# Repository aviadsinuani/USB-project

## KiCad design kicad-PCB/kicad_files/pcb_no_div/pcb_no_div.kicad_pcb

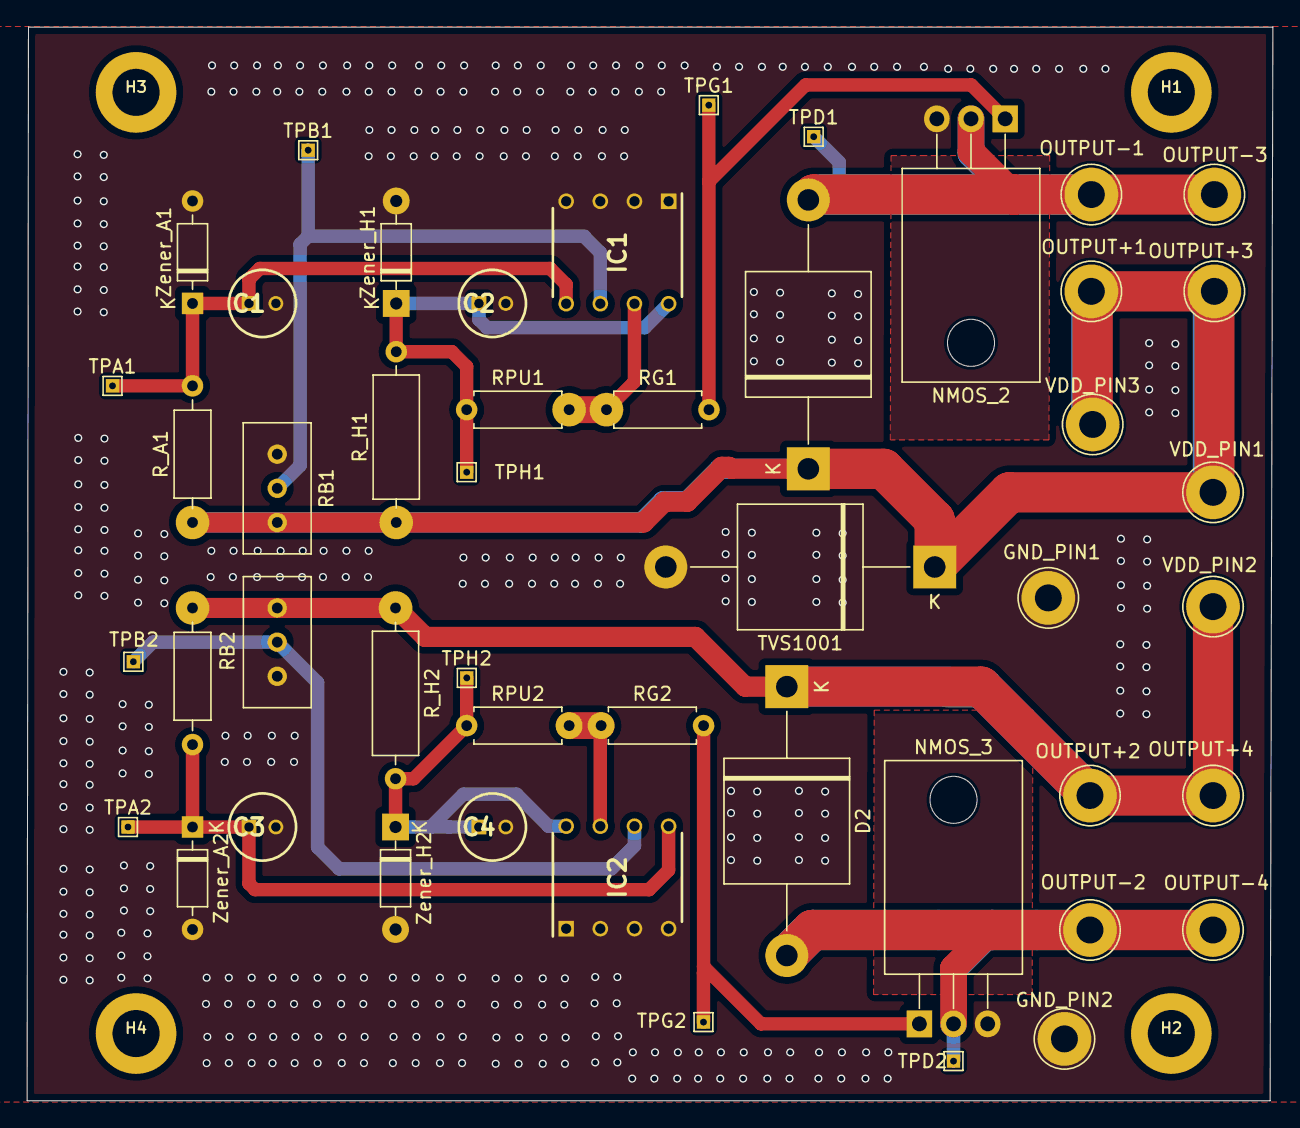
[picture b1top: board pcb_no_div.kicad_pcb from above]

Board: 2 copper layers, 92.7 x 79.9 mm, 52 parts (0 on the bottom side), 15 nets.

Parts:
C1, C2, C3, C4: C_Polarized; CAPPRD200W52D500H1250
D1, D2: 5KP28A; D_P600_R-6_P20.00mm_Horizontal
GND_PIN1, GND_PIN2: TestPoint_THTPad_D4.0mm_Drill2.0mm
H1, H2, H3, H4: MountingHole; screwHole
IC1, IC2: AS393P-E1; DIP762W56P254L930H431Q8N
NMOS_2, NMOS_3: NMOS; TO-220-3_Horizontal_TabDown
OUTPUT+1, OUTPUT+2, OUTPUT+3, OUTPUT+4: TestPoint_THTPad_D4.0mm_Drill2.0mm
OUTPUT-1, OUTPUT-2, OUTPUT-3, OUTPUT-4: TestPoint_THTPad_D4.0mm_Drill2.0mm
RB1, RB2: R_Potentiometer_Trim_US; Potentiometer_Bourns_3296W_Vertical
RG1, RG2: 2.5k; R_Axial_DIN0207_L6.3mm_D2.5mm_P7.62mm_Horizontal
RPU1, RPU2: 2.5k; R_Axial_DIN0207_L6.3mm_D2.5mm_P7.62mm_Horizontal
R_A1, R_A2: 2.5k; R_Axial_DIN0207_L6.3mm_D2.5mm_P10.16mm_Horizontal
R_H1, R_H2: 1K; R_Axial_DIN0309_L9.0mm_D3.2mm_P12.70mm_Horizontal
TPA1, TPA2: A_point; TestPoint_THTPad_1.0x1.0mm_Drill0.5mm
TPB1, TPB2: B_point; TestPoint_THTPad_1.0x1.0mm_Drill0.5mm
TPD1, TPD2: Output-; TestPoint_THTPad_1.0x1.0mm_Drill0.5mm
TPG1, TPG2: Gate; TestPoint_THTPad_1.0x1.0mm_Drill0.5mm
TPH1, TPH2: H_point; TestPoint_THTPad_1.0x1.0mm_Drill0.5mm
TVS1001: 100V; D_P600_R-6_P20.00mm_Horizontal
VDD_PIN1, VDD_PIN2, VDD_PIN3: TestPoint_THTPad_D4.0mm_Drill2.0mm
Zener_A1, Zener_A2: 11V; D_DO-35_SOD27_P7.62mm_Horizontal
Zener_H1, Zener_H2: 16V; D_DO-35_SOD27_P7.62mm_Horizontal

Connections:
GND: C1.2, C2.2, C3.2, C4.2, GND_PIN1.1, GND_PIN2.1, IC1.1 (OUTPUT1), IC1.2 (INPUT1-), IC1.3 (INPUT1+), IC1.4 (GND), IC2.1 (OUTPUT1), IC2.2 (INPUT1-), IC2.3 (INPUT1+), IC2.4 (GND), NMOS_2.3 (S), NMOS_3.3 (S), RB1.3, RB2.3, TVS1001.2 (A), Zener_A1.2 (A), Zener_A2.2 (A), Zener_H1.2 (A), Zener_H2.2 (A)
unnamed: C1.1, IC1.5 (INPUT2+), R_A1.2, TPA1.1, Zener_A1.1 (K)
unnamed: IC1.6 (INPUT2-), RB1.2, TPB1.1
unnamed: IC1.7 (OUTPUT2), RG1.1, RPU1.2
unnamed: C2.1, IC1.8 (VCC), RPU1.1, R_H1.2, TPH1.1, Zener_H1.1 (K)
unnamed: C3.1, IC2.5 (INPUT2+), R_A2.2, TPA2.1, Zener_A2.1 (K)
unnamed: IC2.6 (INPUT2-), RB2.2, TPB2.1
unnamed: IC2.7 (OUTPUT2), RG2.1, RPU2.2
unnamed: C4.1, IC2.8 (VCC), RPU2.1, R_H2.2, TPH2.1, Zener_H2.1 (K)
unnamed: D1.2, NMOS_2.1 (D), OUTPUT-1.1, OUTPUT-3.1, TPD1.1
unnamed: NMOS_2.2 (G), RG1.2, TPG1.1
unnamed: D2.2, NMOS_3.1 (D), OUTPUT-2.1, OUTPUT-4.1, TPD2.1
unnamed: NMOS_3.2 (G), RG2.2, TPG2.1
VDD: D1.1, OUTPUT+1.1, OUTPUT+3.1, RB1.1, R_A1.1, R_H1.1, TVS1001.1 (K), VDD_PIN1.1, VDD_PIN3.1
VDD2: D2.1, OUTPUT+2.1, OUTPUT+4.1, RB2.1, R_A2.1, R_H2.1, VDD_PIN2.1

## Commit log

2025-08-19 Create 1
2025-08-19 Create w
2025-08-19 Create aliexpress
